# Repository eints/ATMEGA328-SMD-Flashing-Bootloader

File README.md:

# ATMEGA328 SMD Bootloader Flashing

This is a little project I built to be able to flash my ATMEGA328 SMD chips with an Arduino bootloader.
There are professional solutions like here https://www.youtube.com/watch?v=GFyr9tVEHzQ. 
But for the 5 to 10 Chips I need to flash from time to time I couldn't justify to buy such a thing. 
I wanted to have something cheap and easy to use. Thus I built my own simple board.

I always use the [Optiloader](https://github.com/WestfW/OptiLoader). 
To flash it to an out-of-factory chip you need to connect the RESET, MISO, MOSI & SCK pins. 
Additionally a crystal and +5V are required. I designed this simple shield for an Uno with the mentioned connections.

The used components are just a 10k pull-up resistor for the RESET pin, a 16MHz crystal with two 22pF capacitors and a few pin headers.

I milled the PCB on my desktop CNC with a 60° V-bit. The resulting PCB looks like this:
| PCB Front      | PCB Back with magnet  |
|------------|-------------|
|   |   | 

To press the chip onto the PCB the 3D printed chip holder is used.

The chip should fit perfectly in the recess. At first the recess was slightly to large. 
I could have reprinted the holder with a smaller recess but roughing the inner walls of the recess with a knives solved the problem for me. 
Now the chip kind of clicks in.
The hole in one corner of the holder marks the chip orientation. It is aligned with the marking impression on the top side of the chip.

| Inserting Chip      | Chip Inserted  |
|------------|-------------|
|   |   | 

Four bolts guarantee the alignment of chip and PCB. I use broken drill/mill bits from my CNC. 
Magnets in the holder and on the backside of the PCB apply slight pressure to ensure a reliable contact.

When the chip is in place the bootloader is flashed.

Here is the flashed chip ready to be used in the next project!

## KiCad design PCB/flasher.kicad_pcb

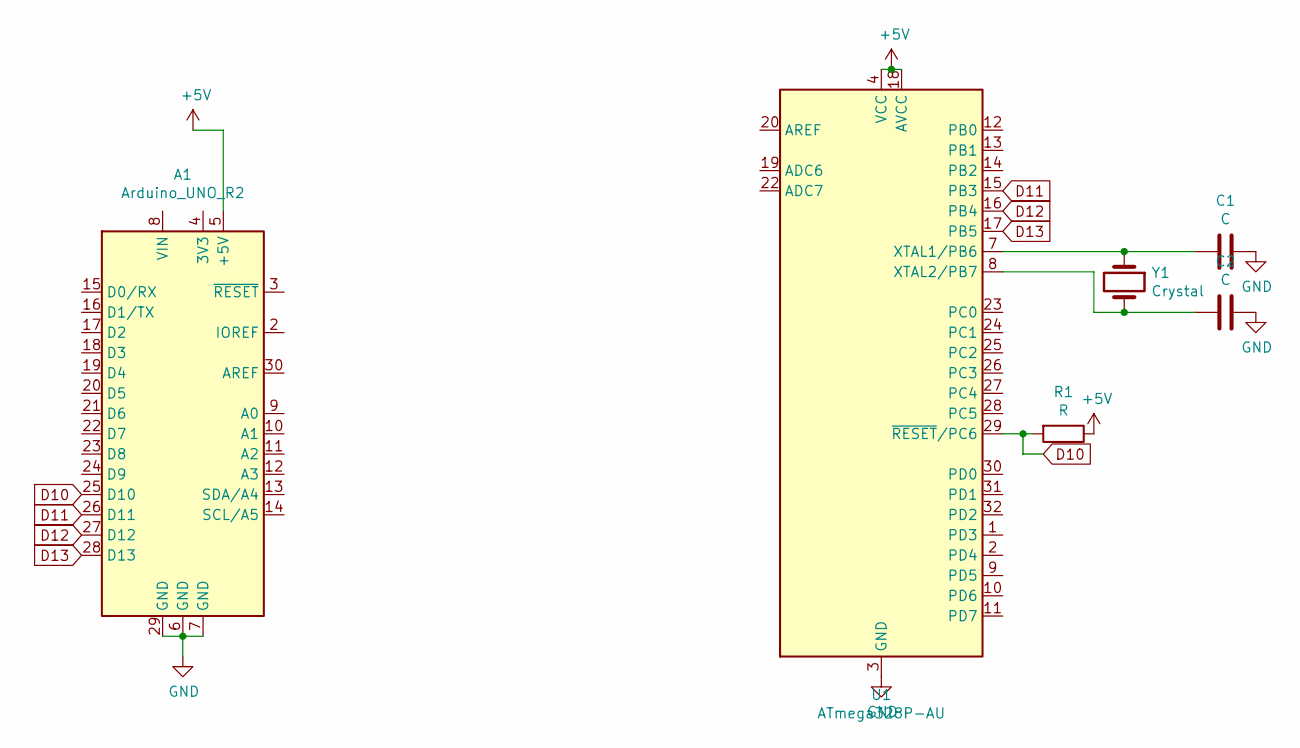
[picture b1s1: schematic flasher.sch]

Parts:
A1: Arduino_UNO_R2
C1, C2: C; C_0805_2012Metric
R1: R; R_0805_2012Metric
U1: ATmega328P-AU; TQFP-32_7x7mm_P0.8mm
Y1: Crystal; Crystal_SMD_HC49-SD

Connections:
+5V: A1.5 (+5V), R1.1, U1.4 (VCC), U1.6 (VCC), U1.18 (AVCC)
D10: A1.25 (D10), R1.2, U1.29 (~RESET~/PC6)
D11: A1.26 (D11), U1.15 (PB3)
D12: A1.27 (D12), U1.16 (PB4)
D13: A1.28 (D13), U1.17 (PB5)
GND: A1.6 (GND), A1.7 (GND), A1.29 (GND), C1.1, C2.1, U1.3 (GND), U1.5 (GND), U1.21 (GND)
unnamed: C1.2, U1.7 (XTAL1/PB6), Y1.1
unnamed: C2.2, U1.8 (XTAL2/PB7), Y1.2

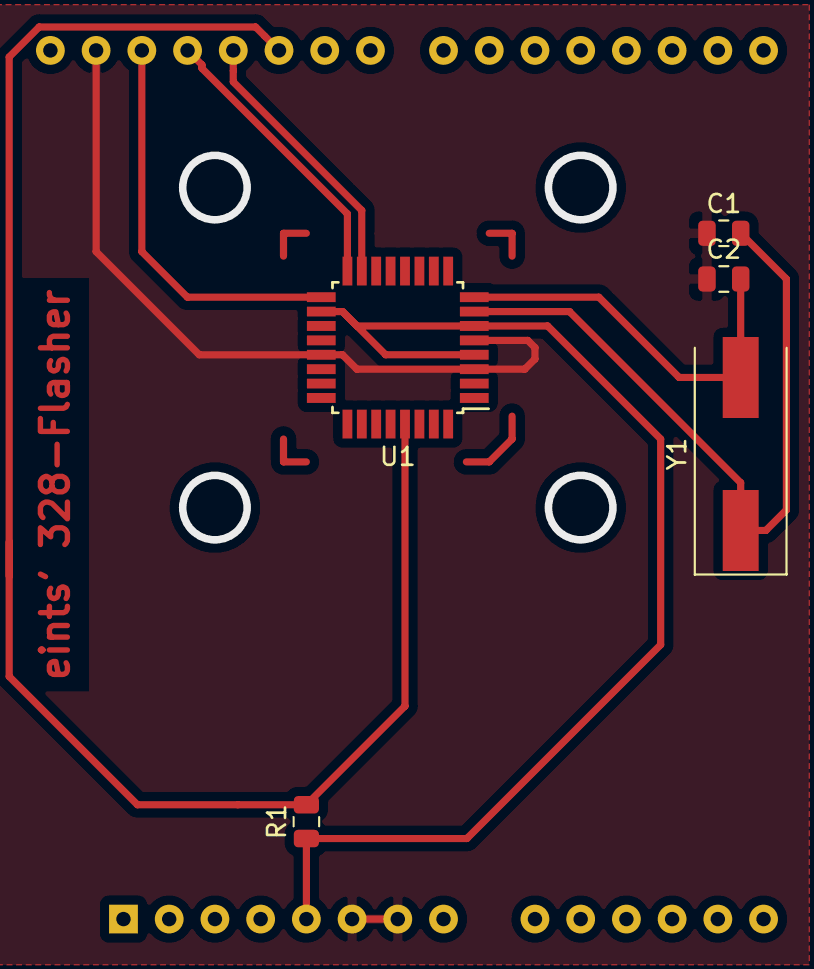
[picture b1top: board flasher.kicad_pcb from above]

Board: 2 copper layers, 6 parts (1 on the bottom side), 8 nets.

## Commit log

2020-04-25 Committing project files
2020-04-25 Added Images
2020-04-25 Readme changes
2020-04-25 asdf
